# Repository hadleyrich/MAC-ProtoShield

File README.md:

MAC ProtoShield
===============
Copyright 2013 nice technology Ltd  
Website: <http://nicegear.co/mac-protoshield>

Based on the Freetronics ProtoShieldShort
<http://www.freetronics.com/pss>

A specially shaped prototyping shield for the Arduino, designed to be
able to clear the RJ45 jack and a PoE Module on an Ethernet Shield
or Freetronics EtherTen. Includes space for a MAC address chip.

Features:

 * Designed to fit a Freetronics EtherTen with an 802.3af PoE module
   installed, or a standard Ethernet Shield.
 * Arduino "R3" header layout.
 * Surface mount pads for an I2C connected EEPROM with built in MAC
   address (MicroChip 24AA02E48).
 * Pads for reset button connected to Arduino reset pin.
 * Parts overlay on both the top and the bottom so you can see what you
   are connecting without having to keep turning the board over.

LICENSE
-------
Licensed under the TAPR Open Hardware License (www.tapr.org/OHL).
See the "LICENSE" file within this repository for the full license
in plain text format.

INSTALLATION
------------
The design is saved as an EAGLE project. EAGLE PCB design software is
available from www.cadsoftusa.com free for non-commercial use. To use
this project download it and place the directory containing these files
into the "eagle" directory on your computer. Then open EAGLE and
navigate to Projects -> eagle -> MAC-ProtoShield.

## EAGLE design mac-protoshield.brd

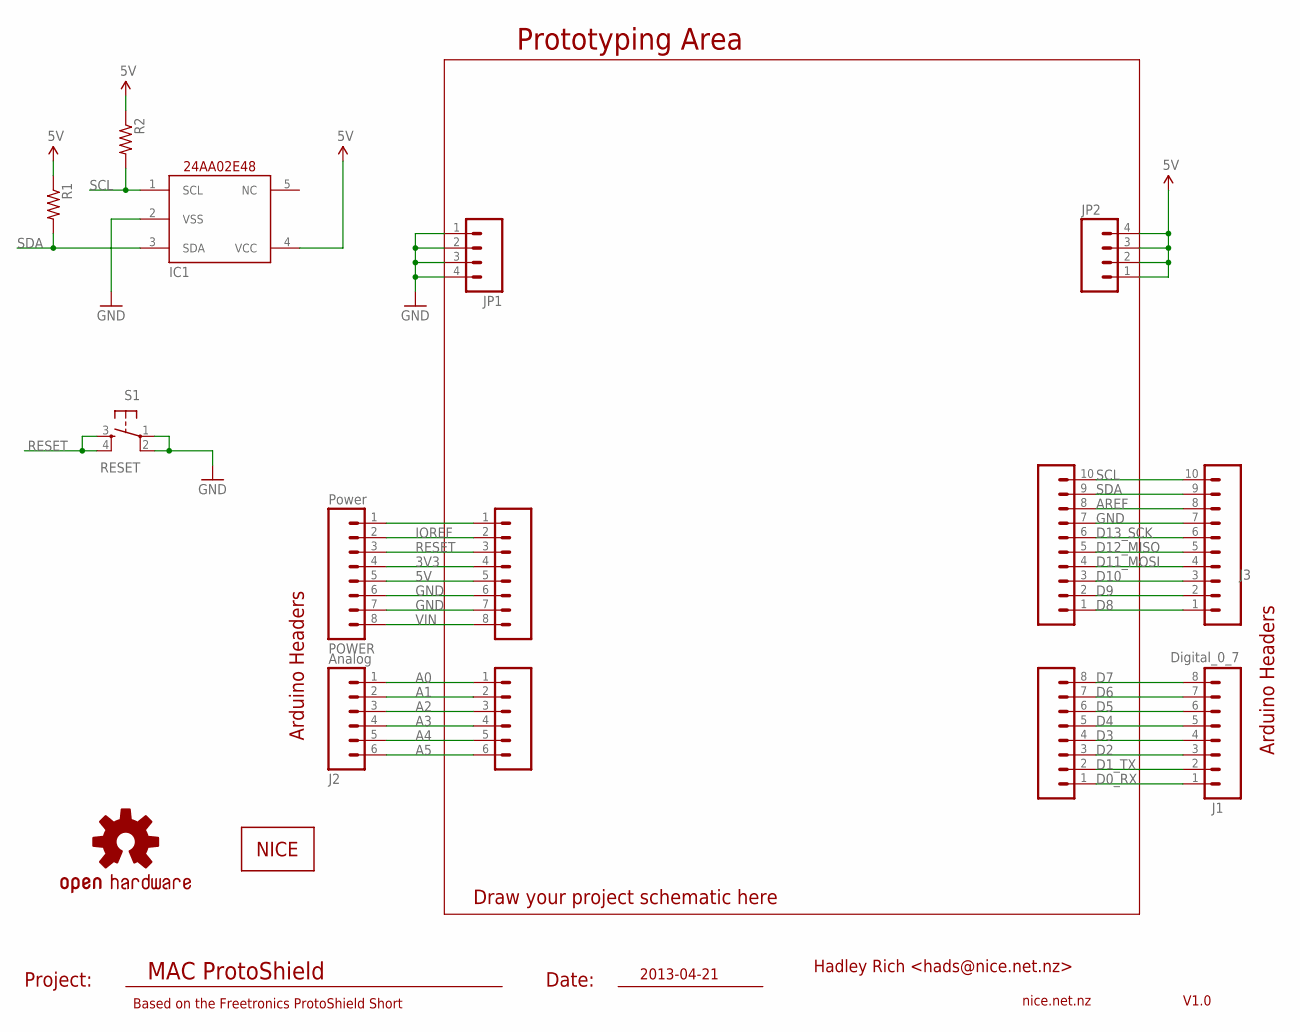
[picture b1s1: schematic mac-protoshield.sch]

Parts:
IC1: 24AA-2E48; SOT23-5
J1: Digital_0_7; 1X08
J2: Analog; 1X06
J3: Digital_8_13; 1X10
JP1, JP2: M04PTH; 1X04
LOGO1: OSHW-LOGOS; OSHW-LOGO-S
POWER: Power; 1X08
R1, R2: RESISTOR0805-RES; 0805
S1: RESET; TACTILE-PTH
SL1: Digital_0_7; 1X08
SL2: Analog; 1X06
SL3: Digital_8_13; 1X10
SLP: Power; 1X08
U$5: NICE-LOGO04; NICE-LOGO-04

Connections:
3V3: POWER.4, SLP.4
5V: IC1.4 (VCC), JP2.1, JP2.2, JP2.3, JP2.4, POWER.5, R1.1, R2.1, SLP.5
A0: J2.1, SL2.1
A1: J2.2, SL2.2
A2: J2.3, SL2.3
A3: J2.4, SL2.4
A4: J2.5, SL2.5
A5: J2.6, SL2.6
AREF: J3.8, SL3.8
D0_RX: J1.1, SL1.1
D1_TX: J1.2, SL1.2
D2: J1.3, SL1.3
D3: J1.4, SL1.4
D4: J1.5, SL1.5
D5: J1.6, SL1.6
D6: J1.7, SL1.7
D7: J1.8, SL1.8
D8: J3.1, SL3.1
D9: J3.2, SL3.2
D10: J3.3, SL3.3
D11_MOSI: J3.4, SL3.4
D12_MISO: J3.5, SL3.5
D13_SCK: J3.6, SL3.6
GND: IC1.2 (VSS), J3.7, JP1.1, JP1.2, JP1.3, JP1.4, POWER.6, POWER.7, S1.1, S1.2, SL3.7, SLP.6, SLP.7
IOREF: POWER.2, SLP.2
unnamed: POWER.1, SLP.1
RESET: POWER.3, S1.3, S1.4, SLP.3
SCL: IC1.1 (SCL), J3.10, R2.2, SL3.10
SDA: IC1.3 (SDA), J3.9, R1.2, SL3.9
VIN: POWER.8, SLP.8

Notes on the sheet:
MAC ProtoShield
V1.0
nice.net.nz
Prototyping Area
Arduino Headers
Project:
Date:
Draw your project schematic here
Based on the Freetronics ProtoShield Short
2013-04-21
Hadley Rich <hads@nice.net.nz>

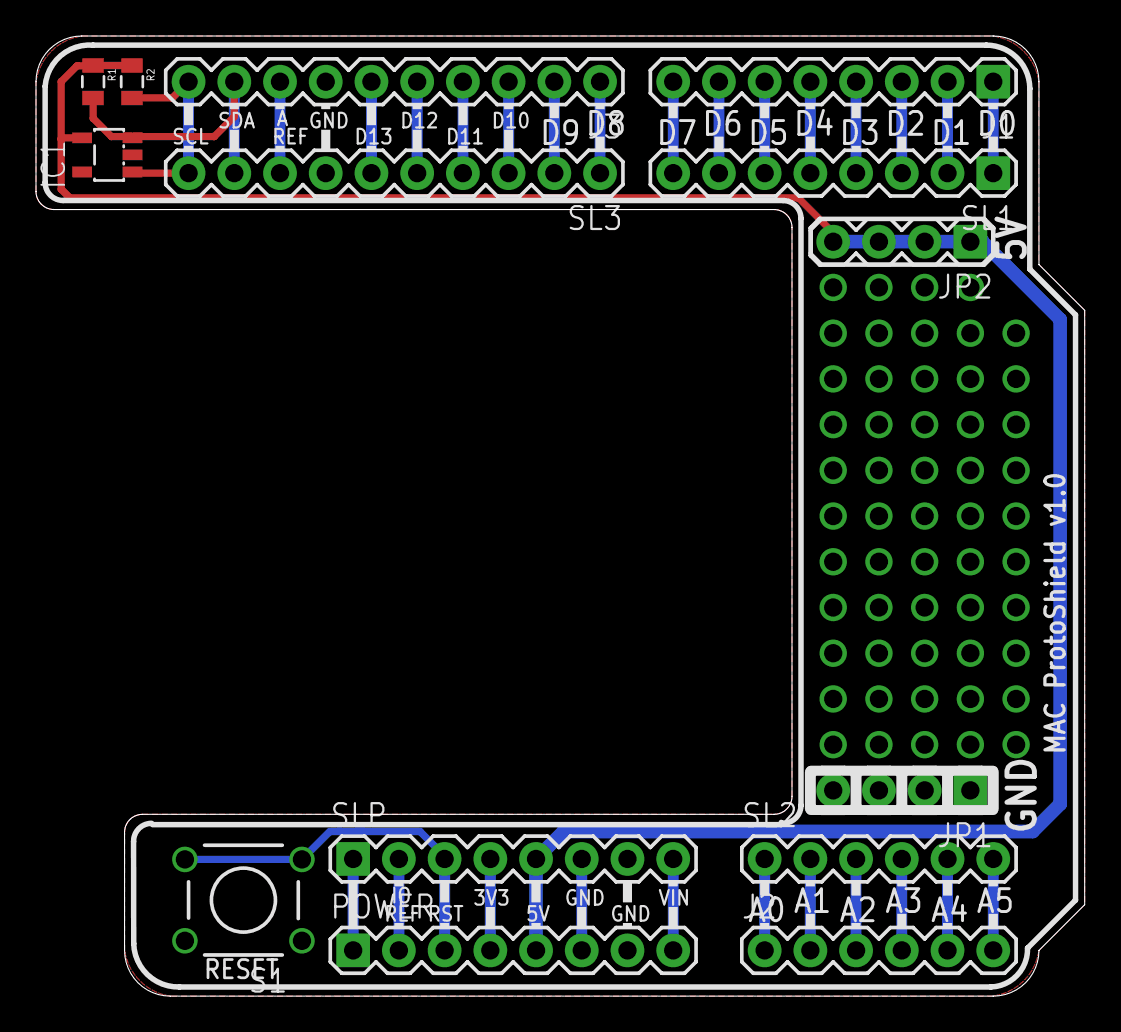
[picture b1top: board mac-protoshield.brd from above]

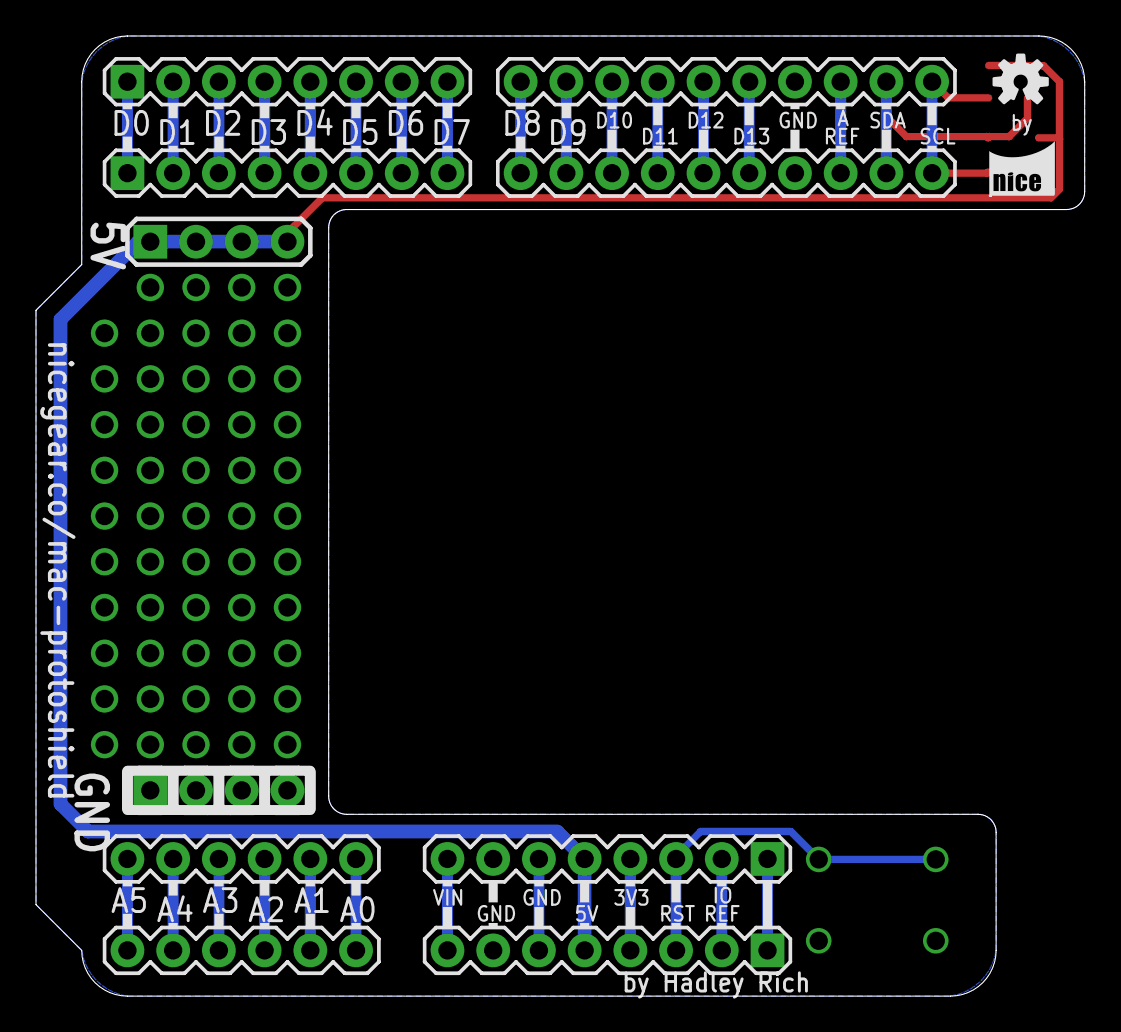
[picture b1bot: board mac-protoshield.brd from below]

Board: 2 copper layers, 58.3 x 53.3 mm, 16 parts (2 on the bottom side), 30 nets.

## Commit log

2013-05-14 Add example Arduino sketch

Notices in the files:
parts and their libraries:
SparkFun-Connectors: Licensing: CC v3.0 Share-Alike You are welcome to use this library for commercial purposes.
